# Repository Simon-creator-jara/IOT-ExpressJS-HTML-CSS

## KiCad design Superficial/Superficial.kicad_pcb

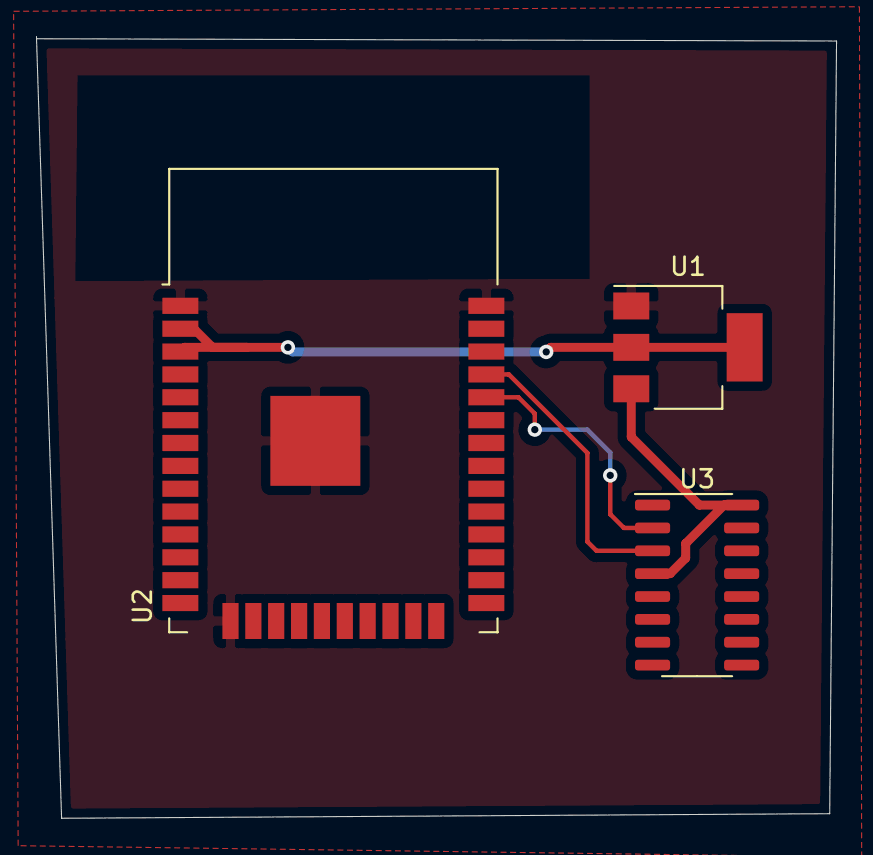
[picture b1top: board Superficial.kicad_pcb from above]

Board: 2 copper layers, 44.5 x 43.4 mm, 3 parts (0 on the bottom side), 5 nets.

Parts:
U1: AMS1117-3.3; SOT-223-3_TabPin2
U2: ESP32-WROOM-32
U3: CH340C; SOIC-16_3.9x9.9mm_P1.27mm

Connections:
+3V3: U1.2, U2.2, U2.3
+5V: U1.3, U3.4, U3.16
GND: U1.1, U2.1, U2.15, U2.38, U2.39
RX_ESP: U2.34, U3.2
TX_ESP: U2.35, U3.3

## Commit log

2023-06-09 Codigos de C, ExpressJS, CSS, HTML
